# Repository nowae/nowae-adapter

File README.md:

# nowae-adapter
A lot of useful adapter boards

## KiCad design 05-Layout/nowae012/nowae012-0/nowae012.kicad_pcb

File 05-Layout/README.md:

# README.md

In this folder you can find the boards design files of project.
* NOWAE004 - NXP Freedom adapter board

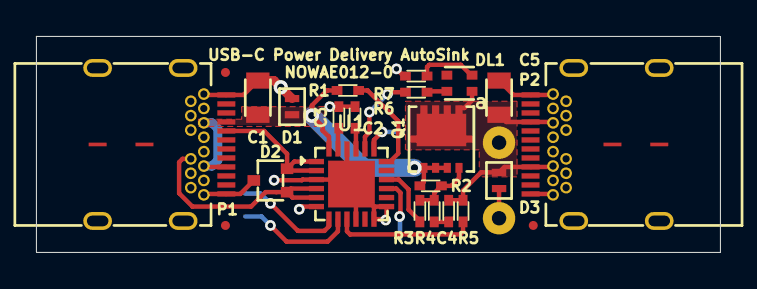
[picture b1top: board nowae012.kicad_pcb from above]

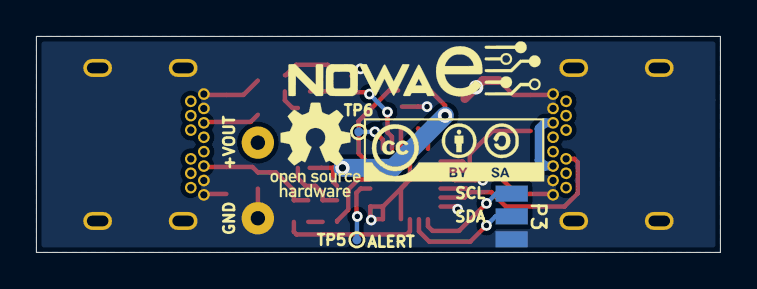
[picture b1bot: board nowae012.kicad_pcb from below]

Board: 2 copper layers, 38.0 x 12.0 mm, 28 parts (3 on the bottom side), 19 nets.

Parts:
C1, C5: 4u7; CAPACITOR-0805
C2, C3: 1u; CAPACITOR-0402
C4: 100n; CAPACITOR-0402
D1, D3: ESDA25P35; QFN1610
D2: ESDA25W; SOT323-3
DL1: RGB; LEDRGB-WE-150066M153000
P1, P2: USB3.1-C; USB3.1-C_WE-632723300011
P3: I2C; CONN-PAD-3x1-1.27
Q1: STL6P3LLH6; TDSON8_3.2x3.2_0.65
R1, R5: 1k; RESISTOR-0402
R2: 100k; RESISTOR-0402
R3, R6, R7: 22k; RESISTOR-0402
R4: 100; RESISTOR-0402
TP1, TP2: TEST_POINT; PAD_THT_0.8x1.8
TP5, TP6: TEST_POINT; TESTPOINT-0.5MM-SMD
U1: STUSB4500LQTR; QFN24_4x4_0.5_24+1
VAL**: FIDUCIALMARK_0.5MM_1MM
VAL**#2, VAL**#3: FIDUCIALMARK_0.5MM_1MM

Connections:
/+2V7: C3.1, U1.23
GND: C1.1, C2.2, C3.2, C5.1, D1.1, D2.3, D3.1, P1.A1, P1.A12, P1.B1, P1.B12, P1.S1, P2.A1, P2.A12, P2.B1, P2.B12, P2.S1, P3.3, R7.2, TP2.1, U1.3, U1.6, U1.10, U1.12, U1.13, U1.22, U1.25
unnamed: C1.2, D1.2, P1.A4, P1.A9, P1.B4, P1.B9, Q1.1, Q1.2, Q1.3, R1.1, R2.1, U1.24
unnamed: C2.1, U1.21
unnamed: C4.1, C5.2, D3.2, DL1.4, P2.A4, P2.A9, P2.B4, P2.B9, Q1.5, R5.1, TP1.1
unnamed: C4.2, R4.2
unnamed: D2.1, P1.B5, U1.4, U1.5
unnamed: D2.2, P1.A5, U1.1, U1.2
unnamed: DL1.1, R6.1
unnamed: DL1.3, R7.1
unnamed: P3.1, U1.7
unnamed: P3.2, U1.8
unnamed: Q1.4, R2.2, R3.1, R4.1
unnamed: R1.2, U1.18
unnamed: R3.2, U1.16
unnamed: R5.2, U1.9
unnamed: R6.2, U1.20
unnamed: TP5.1, U1.15
unnamed: TP6.1, U1.19

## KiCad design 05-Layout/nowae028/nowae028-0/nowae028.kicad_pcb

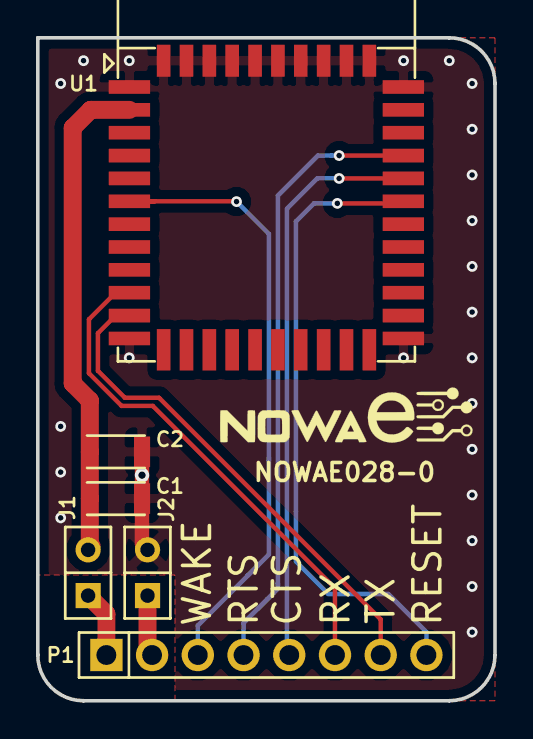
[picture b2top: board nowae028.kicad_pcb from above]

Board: 2 copper layers, 25.4 x 36.8 mm, 6 parts (0 on the bottom side), 10 nets.

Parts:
C1: 10u; CAPACITOR-1206
C2: 100n; CAPACITOR-1206
J1, J2: JUMPER-2; CONN-STRIP-2x1-2.54
P1: CONN; CONN-HOLE_8x1_2.54
U1: AMW037; WIFI-AMW037

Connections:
+3.3V: J1.1, P1.1
+VDD: C1.1, C2.1, J1.2, U1.2
/WIFI_CTS: P1.5, U1.30
/WIFI_RESET: P1.8, U1.29
/WIFI_RTS: P1.4, U1.31
/WIFI_RX: P1.6, U1.10
/WIFI_TX: P1.7, U1.11
/WIFI_WAKE: P1.3, U1.6
GND: J2.1, P1.2
GND-ISO: C1.2, C2.2, J2.2, U1.1, U1.12, U1.23, U1.34, U1.35, U1.36, U1.37, U1.38, U1.39, U1.40, U1.41, U1.42, U1.43, U1.44

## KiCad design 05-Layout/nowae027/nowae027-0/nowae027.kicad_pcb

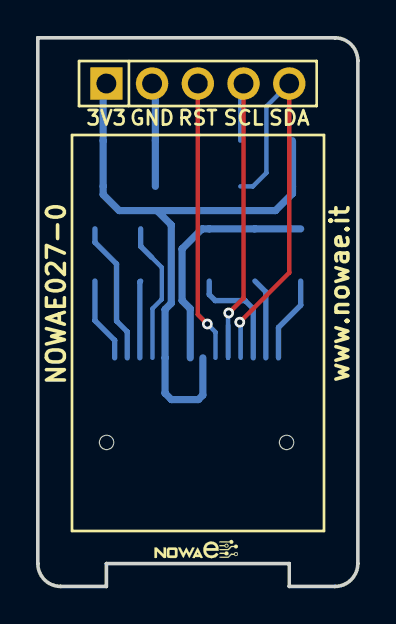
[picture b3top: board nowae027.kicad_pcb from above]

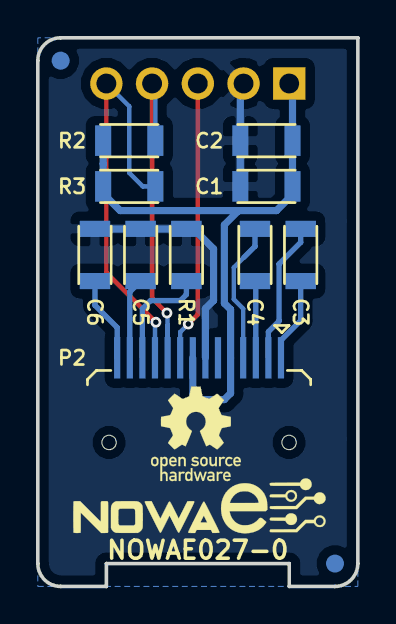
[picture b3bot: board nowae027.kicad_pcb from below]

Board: 2 copper layers, 17.8 x 30.5 mm, 14 parts (12 on the bottom side), 12 nets.

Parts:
C1, C3, C4, C5: 2u2; CAPACITOR-1206
C2: 100n; CAPACITOR-1206
C6: 10u; CAPACITOR-1206
P1: CONN; CONN-HOLE_5x1_2.54
P2: OLED; DISPLAY-RAYSTAR-REX004864A
R1: 330k; RESISTOR-1206
R2, R3: 4k7; RESISTOR-1206
VAL**: FIDUCIALMARK_1MM_2MM
VAL**#2: FIDUCIALMARK_1MM_2MM
VAL?: DISPLAY-RAYSTAR-REX004864A_ONLY3D

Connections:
+3.3V: C1.2, C2.2, P1.1, P2.5, P2.8, R2.1, R3.1
/OLED_RESET: P1.3, P2.9
/OLED_SCL: P1.4, P2.10, R2.2
/OLED_SDA: P1.5, P2.11, R3.2
GND: C1.1, C2.1, C5.1, C6.1, P1.2, P2.7, R1.2
unnamed: C3.1, P2.1
unnamed: C3.2, P2.2
unnamed: C4.1, P2.3
unnamed: C4.2, P2.4
unnamed: C5.2, P2.13
unnamed: C6.2, P2.14
unnamed: P2.12, R1.1

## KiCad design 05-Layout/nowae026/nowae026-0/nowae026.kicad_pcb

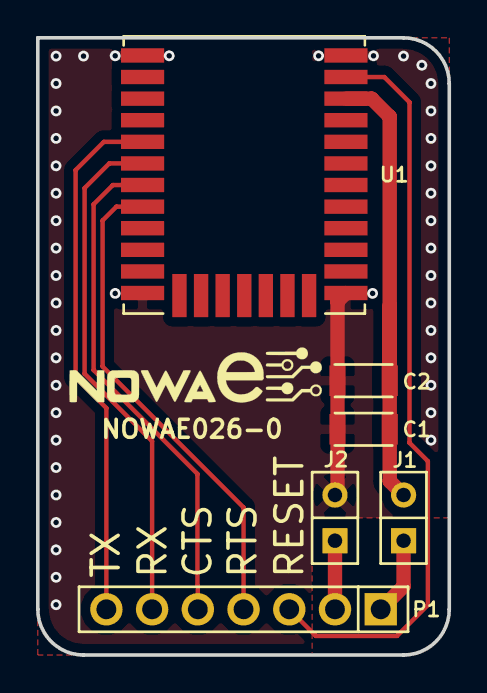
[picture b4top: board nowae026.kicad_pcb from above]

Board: 2 copper layers, 22.9 x 34.3 mm, 6 parts (0 on the bottom side), 9 nets.

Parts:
C1: 4u7; CAPACITOR-1206
C2: 100n; CAPACITOR-1206
J1, J2: JUMPER-2; CONN-STRIP-2x1-2.54
P1: CONN; CONN-HOLE_7x1_2.54
U1: BGM111A256V21; BLE-BGM111A256V2

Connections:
+3.3V: J1.1, P1.1
+VDD: C1.1, C2.1, J1.2, U1.29
/BLE_CTS: P1.5, U1.7
/BLE_RESET: P1.3, U1.30
/BLE_RTS: P1.4, U1.8
/BLE_RX: P1.6, U1.6
/BLE_TX: P1.7, U1.5
GND: J2.1, P1.2
GND-ISO: C1.2, C2.2, J2.2, U1.1, U1.12, U1.20, U1.31

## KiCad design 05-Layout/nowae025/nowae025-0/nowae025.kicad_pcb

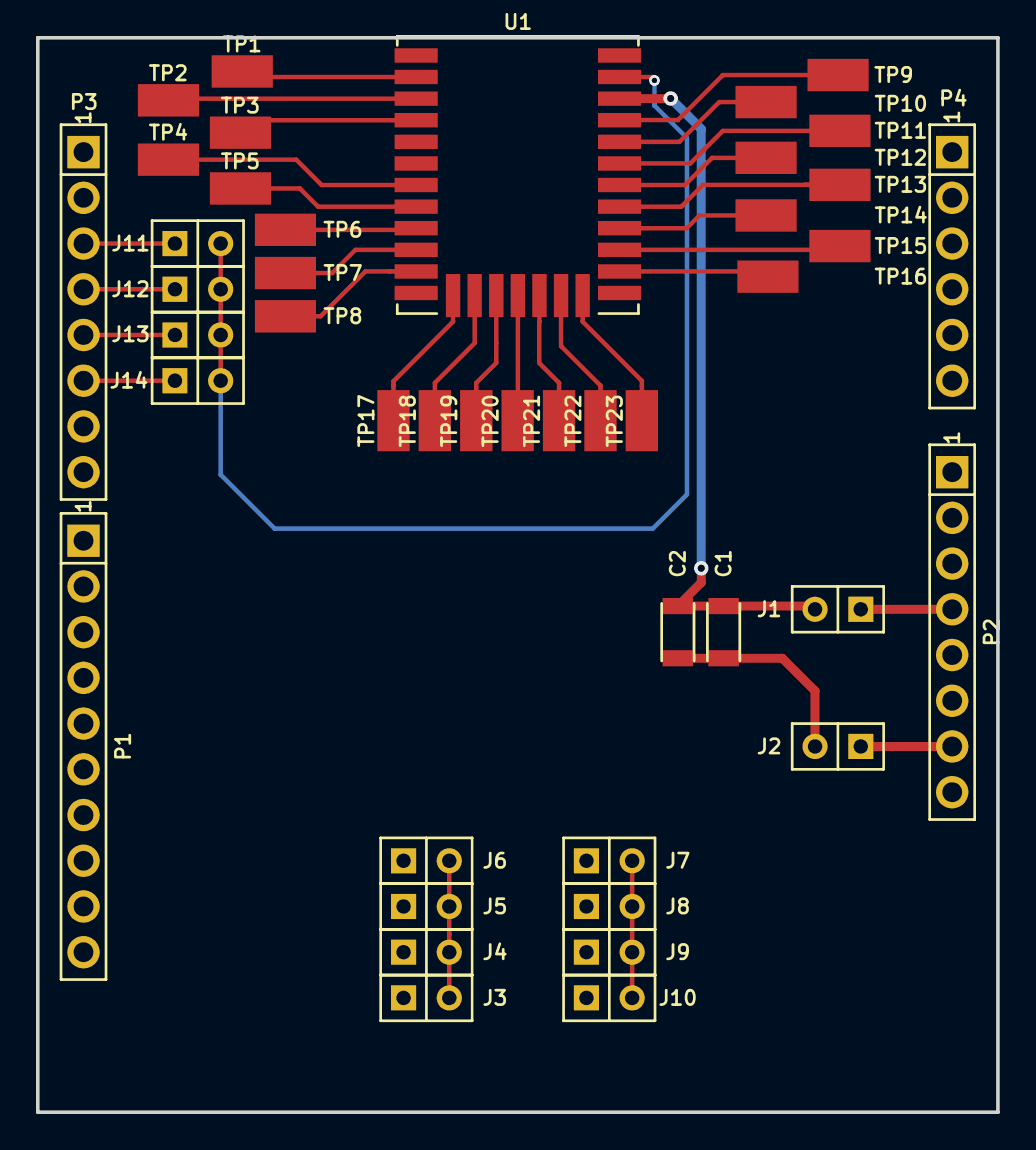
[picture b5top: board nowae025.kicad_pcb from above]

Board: 2 copper layers, 53.3 x 59.7 mm, 44 parts (0 on the bottom side), 42 nets.

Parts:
C1: 4u7; CAPACITOR-1206
C2: 100n; CAPACITOR-1206
J1, J2, J3, J4, J5, J6, J7, J8, J9, J10, J11, J12, J13, J14: JUMPER-2; CONN-STRIP-2x1-2.54
P1: ARD_RIGHT2; SOCKET_10x1_2.54_WE-61301011821
P2: ARD_LEFT2; SOCKET_8x1_2.54_WE-61300811821
P3: ARD_RIGHT1; SOCKET_8x1_2.54_WE-61300811821
P4: ARD_LEFT1; SOCKET_6x1_2.54_WE-61300611821
TP1, TP2, TP3, TP4, TP5, TP6, TP7, TP8, TP9, TP10, TP11, TP12, TP13, TP14, TP15, TP16, TP17, TP18, TP19, TP20, TP21, TP22, TP23: TEST_POINT; TESTPOINT-KEYSTONE-5015
U1: BGM111A256V2; BLE-BGM111A256V2

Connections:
+3.3V: J1.1, P2.4
+VDD: C1.1, C2.1, J1.2, U1.29
/ARDUINO_A0: J9.1, P4.1
/ARDUINO_A1: J5.1, P4.2
/ARDUINO_A4: J10.1, P4.5
/ARDUINO_A5: J6.1, P4.6
/ARDUINO_D0: J7.1, P3.1
/ARDUINO_D1: J3.1, P3.2
/ARDUINO_D2: J11.1, P3.3
/ARDUINO_D3: J12.1, P3.4
/ARDUINO_D4: J13.1, P3.5
/ARDUINO_D5: J14.1, P3.6
/ARDUINO_D14: J8.1, P1.9
/ARDUINO_D15: J4.1, P1.10
/BLE_RESET: J11.2, J12.2, J13.2, J14.2, U1.30
/BLE_RX: J7.2, J8.2, J9.2, J10.2, U1.6
/BLE_TX: J3.2, J4.2, J5.2, J6.2, U1.5
GND: J2.1, P1.7, P2.6, P2.7
GND-ISO: C1.2, C2.2, J2.2, U1.1, U1.12, U1.20, U1.31
unnamed: TP1.1, U1.2
unnamed: TP2.1, U1.3
unnamed: TP3.1, U1.4
unnamed: TP4.1, U1.7
unnamed: TP5.1, U1.8
unnamed: TP6.1, U1.9
unnamed: TP7.1, U1.10
unnamed: TP8.1, U1.11
unnamed: TP9.1, U1.28
unnamed: TP10.1, U1.27
unnamed: TP11.1, U1.26
unnamed: TP12.1, U1.25
unnamed: TP13.1, U1.24
unnamed: TP14.1, U1.23
unnamed: TP15.1, U1.22
unnamed: TP16.1, U1.21
unnamed: TP17.1, U1.13
unnamed: TP18.1, U1.14
unnamed: TP19.1, U1.15
unnamed: TP20.1, U1.16
unnamed: TP21.1, U1.17
unnamed: TP22.1, U1.18
unnamed: TP23.1, U1.19

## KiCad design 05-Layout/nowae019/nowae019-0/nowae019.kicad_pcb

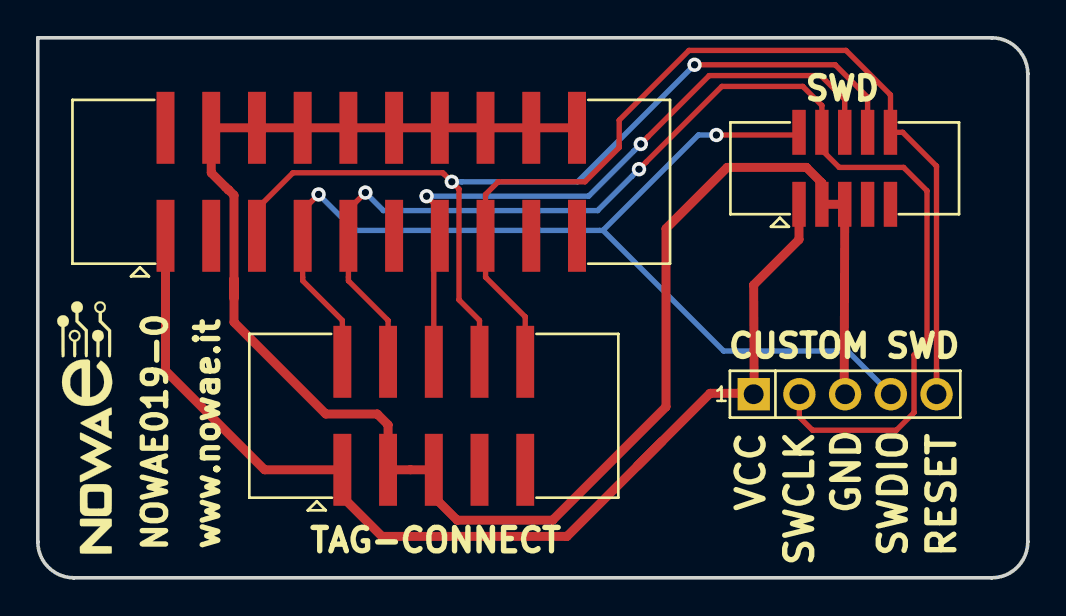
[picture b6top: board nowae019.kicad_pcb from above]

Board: 2 copper layers, 55.0 x 30.0 mm, 4 parts (0 on the bottom side), 7 nets.

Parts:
P1: U-MULTILINK-SMALL; STRIP_5x2_1.27_SMD-AMPHENOL-20021521_00010T1LF
P2: U-MULTILINK; STRIP-BOX_10x2_2.54_SMD-WE-61202020621
P3: TAG; STRIP-BOX_5x2_2.54_SMD-WE-61201020621
P4: CUSTOM; STRIP_5x1_2.54_WE-61300511121

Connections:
/PROG_GND: P1.3, P1.5, P2.4, P2.6, P2.8, P2.10, P2.12, P2.14, P2.16, P2.18, P2.20, P3.3, P3.5, P4.3
/PROG_RESET: P1.10, P2.15, P3.10, P4.5
/PROG_SW0: P1.6, P2.13, P3.6
/PROG_SWCLK: P1.4, P2.9, P3.4, P4.2
/PROG_SWDIO: P1.2, P2.7, P3.2, P4.4
/PROG_TDI: P1.8, P2.5, P3.8
/PROG_VCC: P1.1, P2.1, P3.1, P4.1

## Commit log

2017-02-04 Added project structure
2017-02-04 Added kicad library as submodule
2017-02-06 Removed libkicad sub-module
2017-02-23 Started development of NOWAE004, matrix board for freedom development board
2017-02-27 Added spare LEDs, protection for power supply and some component informations
2017-02-28 Added all component informations. The BOM is complete
2017-03-03 Added enumeration into schematich
2017-03-06 NOWAE004: Changed symbol of switching component
2017-03-06 NOWAE004: added netlist and started PCB development
2017-03-08 NOWAE004: Added last footprint and updated netlist
2017-03-08 NOWAE004: ended PCB development. TODO is fiducial, logos, license and hole in GND plane
2017-05-28 Schematic updated with revision date and added the schematics history
2017-05-28 Added fiducials, logo and license.
2017-05-28 Moved PDF files of schematics into correct directory
2017-05-28 Smal silkscreen fix
2017-05-28 Added gerber files for productions
2017-05-28 Updated gerber files: small fix on GND plane
2018-10-23 Added kicad project for NOWAE019 board
2018-10-23 Added 10x2 connector for device like Segger or other
2018-10-23 Fixed footprint and netlist (nowae019-0)
2018-10-23 Placed components and designed the edge-cuts (nowae019-0)
2018-10-23 Added NOWAE logo (nowae019-0)
2018-10-23 Started routing (nowae019-0)
2018-10-23 Ended routing. Added logos and silkscreen informations. (nowae019-0)
2018-10-24 Added production files. BOM missing.
2018-10-24 Added revision 0 of BOM for NOWAE019-0
2019-03-19 Start schematic of NOWAE025
2019-03-20 Schematic annotation, first component association and pcb file creation (nowae025)
2019-03-20 Added gitignore file
2019-03-21 Added missing footprint. Started component placement (nowae025)
2019-03-26 Added testpoint and started routing (nowae025)
2019-03-28 Started project (nowae026)
2019-03-29 Ended schematic and started PCB (nowae026)
2019-03-29 WiP on PCB (nowae026)
2019-04-01 Ended PCB design (nowae026)
2019-04-05 Started schematic (nowae027)
2019-04-08 Defined board dimension and placed components (nowae027)
2019-04-08 Added first release of gerber files (nowae026)
2019-04-09 Ended routing (nowae027)
2019-04-09 Added first release of gerber files (nowae027)
2019-04-18 Added first version of schematic (nowae028)
2019-04-19 Ended schematic, started PCB (nowae028).
2019-04-23 Ended PCB: fixed silkscreen, net, and ground plane (nowae028)
2019-04-23 Added first gerber version (nowae028)
2019-10-03 Added production documents (nowae019-0)
2019-10-03 Fixed production files name
2019-10-03 Renamed directory 04-Assembly (nowae019-0)
2019-10-03 Moved assembly files (nowae019-0)
2020-02-02 Added project (nowae012-0)
2020-02-02 Added gerber and schematic (nowae012-0)
2020-10-17 WiP: schematic and layout (nowae012-0)
2020-10-17 Added gerber (nowae012-0)
2020-10-17 Removed old gerber (nowae012-0)
